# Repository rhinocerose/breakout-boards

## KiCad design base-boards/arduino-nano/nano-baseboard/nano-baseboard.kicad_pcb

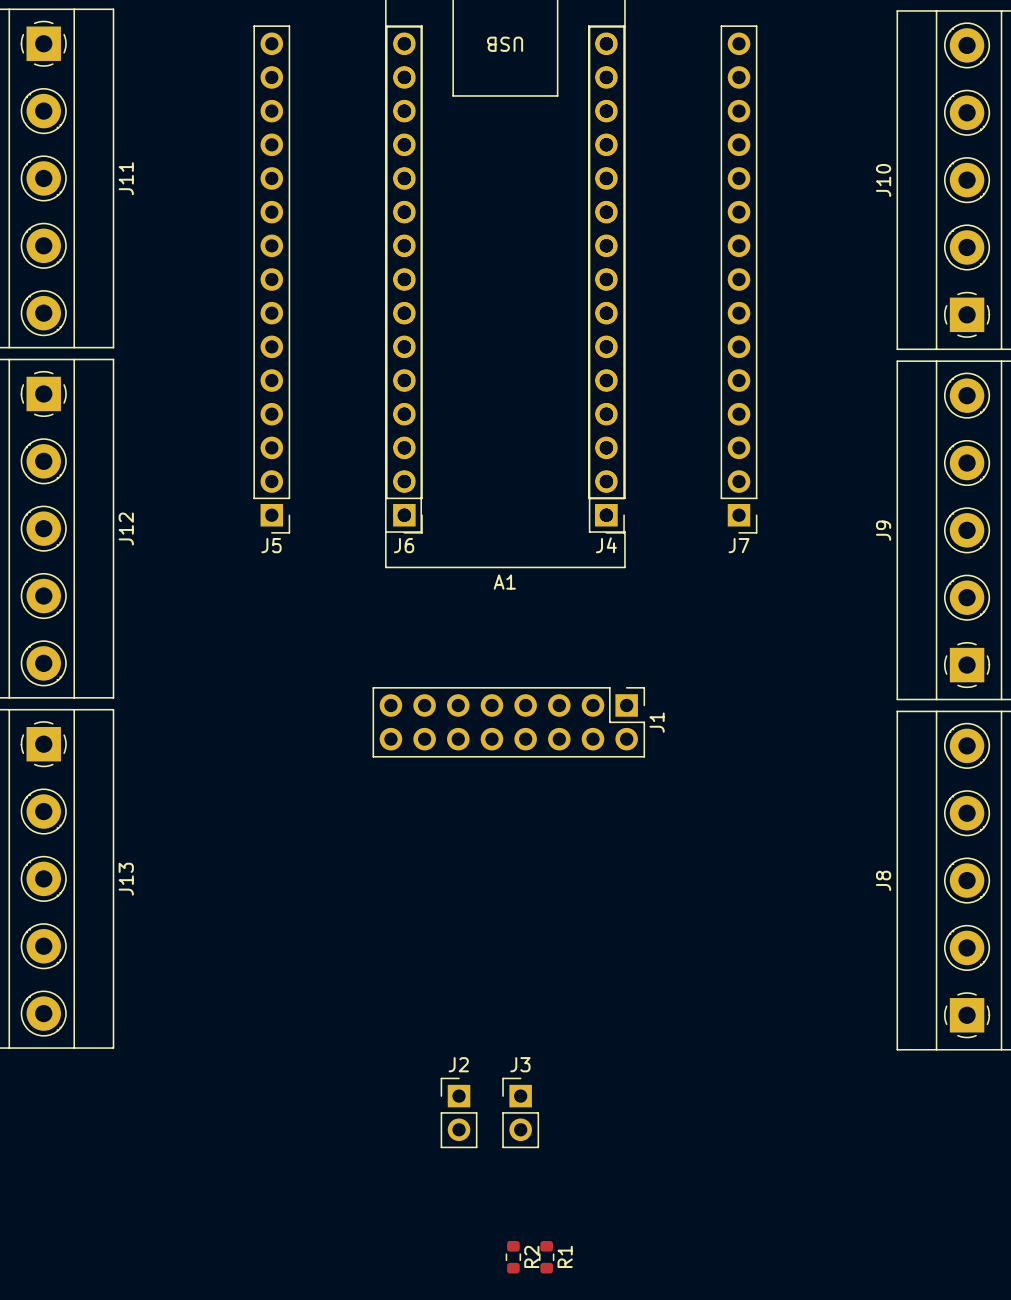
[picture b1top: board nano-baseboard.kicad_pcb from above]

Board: 2 copper layers, 16 parts (0 on the bottom side), 30 nets.

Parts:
A1: Arduino_Nano_v3.x; Arduino_Nano
J1: Conn_02x08_Odd_Even; PinHeader_2x08_P2.54mm_Vertical
J2, J3: Conn_01x02_Pin; PinHeader_1x02_P2.54mm_Vertical
J4, J5, J6, J7: Conn_01x15; PinHeader_1x15_P2.54mm_Vertical
J8, J9, J10, J11, J12, J13: Screw_Terminal_01x05; TerminalBlock_Phoenix_MKDS-1,5-5-5.08_1x05_P5.08mm_Horizont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
R1, R2: R_Small_US; R_0603_1608Metric

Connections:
3v3: A1.17 (3V3), J1.1, J1.2, J5.14, J6.14, J11.2
5v: A1.27 (+5V), J1.3, J1.4, J2.1, J3.1, J5.4, J6.4, J13.2
GND: A1.4 (GND), A1.29 (GND), J1.5, J1.6, J4.4, J5.2, J6.2, J7.4, J8.4, J13.4
I2C_SCL: A1.24 (A5), J1.8, J5.7, J6.7, J12.4, R2.2
I2C_SDA: A1.23 (A4), J1.7, J5.8, J6.8, J12.3, R1.2
unnamed: A1.19 (A0), J5.12, J6.12, J11.4
unnamed: A1.20 (A1), J5.11, J6.11, J11.5
unnamed: A1.21 (A2), J5.10, J6.10, J12.1
unnamed: A1.22 (A3), J5.9, J6.9, J12.2
unnamed: A1.25 (A6), J5.6, J6.6, J12.5
unnamed: A1.26 (A7), J5.5, J6.5, J13.1
unnamed: A1.18 (AREF), J5.13, J6.13, J11.3
unnamed: A1.2 (D0/RX), J4.2, J7.2, J8.2
unnamed: A1.1 (D1/TX), J4.1, J7.1, J8.1
unnamed: A1.5 (D2), J4.5, J7.5, J8.5
unnamed: A1.6 (D3), J4.6, J7.6, J9.1
unnamed: A1.7 (D4), J4.7, J7.7, J9.2
unnamed: A1.8 (D5), J4.8, J7.8, J9.3
unnamed: A1.9 (D6), J4.9, J7.9, J9.4
unnamed: A1.10 (D7), J4.10, J7.10, J9.5
unnamed: A1.11 (D8), J4.11, J7.11, J10.1
unnamed: A1.12 (D9), J4.12, J7.12, J10.2
unnamed: A1.13 (D10), J4.13, J7.13, J10.3
unnamed: J2.2, R1.1
unnamed: J3.2, R2.1
unnamed: J5.1, J6.1, J13.5
RST: A1.3 (~RESET), A1.28 (~RESET), J4.3, J5.3, J6.3, J7.3, J8.3, J13.3
SPI_MISO: A1.15 (D12), J1.10, J4.15, J7.15, J10.5
SPI_MOSI: A1.14 (D11), J1.9, J4.14, J7.14, J10.4
SPI_SCK: A1.16 (D13), J1.11, J5.15, J6.15, J11.1

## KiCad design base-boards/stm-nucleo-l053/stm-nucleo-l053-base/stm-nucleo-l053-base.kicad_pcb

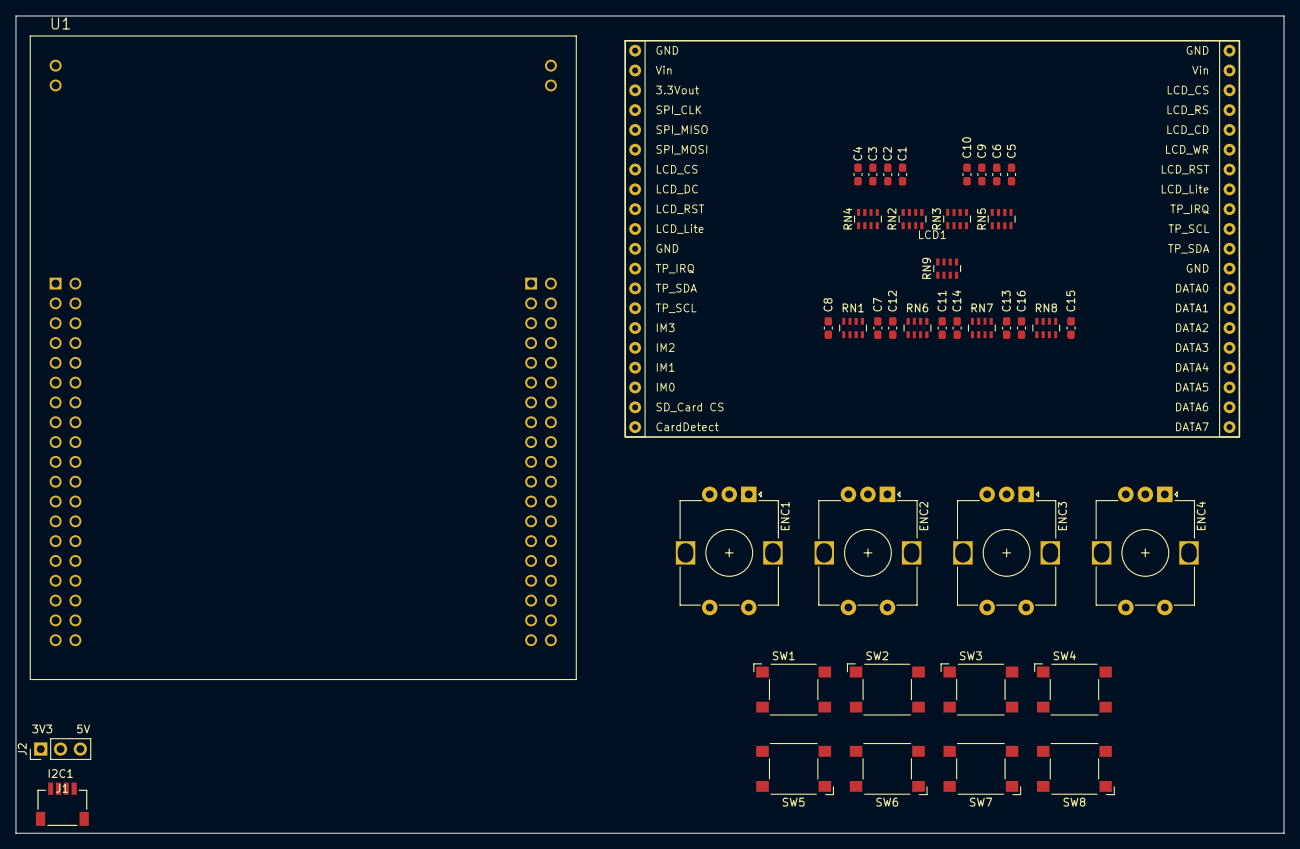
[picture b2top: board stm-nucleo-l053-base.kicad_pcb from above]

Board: 2 copper layers, 162.6 x 104.8 mm, 41 parts (0 on the bottom side), 50 nets, no tracks yet.

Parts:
C1, C2, C3, C4, C5, C6, C9, C10: 10uF; C_0603_1608Metric_Pad1.08x0.95mm_HandSolder
C7, C8, C11, C12, C13, C14, C15, C16: 10nF; C_0603_1608Metric_Pad1.08x0.95mm_HandSolder
ENC1, ENC2, ENC3, ENC4: RotaryEncoder_Switch; RotaryEncoder_Alps_EC12E-Switch_Vertical_H20mm
J1: Qwiic-SM04B-SRSS-TBLFSN; CONN_Qwiic_SM04B_JST
J2: Conn_01x03; PinHeader_1x03_P2.54mm_Vertical
LCD1: Adafruit_2090_Display
RN1, RN2, RN3, RN6, RN7, RN8: 10k_Parallel; R_Array_Concave_4x0603
RN4, RN5: 1k_Parallel; R_Array_Concave_4x0603
RN9: 4k7_Parallel; R_Array_Concave_4x0603
SW1, SW2, SW3, SW4, SW5, SW6, SW7, SW8: SW_SPST; SW_SPST_Omron_B3FS-101xP
U1: NUCLEO-L053R8; MODULE_NUCLEO-L053R8

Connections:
+3.3V: RN1.6 (R3.2), RN1.7 (R2.2), RN2.5 (R4.2), RN2.6 (R3.2), RN2.7 (R2.2), RN2.8 (R1.2), RN3.5 (R4.2), RN3.6 (R3.2), RN3.7 (R2.2), RN3.8 (R1.2), RN6.6 (R3.2), RN6.7 (R2.2), RN7.6 (R3.2), RN7.7 (R2.2), RN8.6 (R3.2), RN8.7 (R2.2), RN9.5 (R4.2), RN9.6 (R3.2), RN9.7 (R2.2), RN9.8 (R1.2)
+3V3: J2.1, U1.CN7_16 (+3V3)
+5V: J2.3, LCD1.2 (Vin), U1.CN7_18 (+5V)
BUTTON1: C1.2, RN4.1 (R1.1)
BUTTON2: C2.2, RN4.2 (R2.1)
BUTTON3: C3.2, RN4.3 (R3.1)
BUTTON4: C4.2, RN4.4 (R4.1)
BUTTON5: C5.2, RN5.1 (R1.1)
BUTTON6: C6.2, RN5.2 (R2.1)
BUTTON7: C9.2, RN5.3 (R3.1)
BUTTON8: C10.2, RN5.4 (R4.1)
ENC1_A: C7.1, RN1.5 (R4.2)
ENC1_B: C8.1, RN1.8 (R1.2)
ENC1_BUTTON: ENC1.S2, RN9.1 (R1.1)
ENC2_A: C11.1, RN6.5 (R4.2)
ENC2_B: C12.1, RN6.8 (R1.2)
ENC2_BUTTON: ENC2.S2, RN9.2 (R2.1)
ENC3_A: C13.1, RN7.5 (R4.2)
ENC3_B: C14.1, RN7.8 (R1.2)
ENC3_BUTTON: ENC3.S2, RN9.3 (R3.1)
ENC4_A: C15.1, RN8.5 (R4.2)
ENC4_B: C16.1, RN8.8 (R1.2)
ENC4_BUTTON: ENC4.S2, RN9.4 (R4.1)
GND: C1.1, C2.1, C3.1, C4.1, C5.1, C6.1, C7.2, C8.2, C9.1, C10.1, C11.2, C12.2, C13.2, C14.2, C15.2, C16.2, ENC1.C, ENC1.S1, ENC2.C, ENC2.S1, ENC3.C, ENC3.S1, ENC4.C, ENC4.S1, J1.1, LCD1.1 (GND), SW1.2 (B), SW2.2 (B), SW3.2 (B), SW4.2 (B), SW5.2 (B), SW6.2 (B), SW7.2 (B), SW8.2 (B), U1.CN7_8 (GND_8), U1.CN7_19 (GND_19), U1.CN7_20 (GND_20), U1.CN7_22 (GND_22), U1.CN10_9 (GND_9), U1.CN10_20 (GND_20), U1.CN11_1 (GND_CN11_1), U1.CN11_2 (GND_CN11_2), U1.CN12_1 (GND_CN12_1), U1.CN12_2 (GND_CN12_2)
I2C1_SCL: J1.4, LCD1.14 (TP_SCL), U1.CN10_3 (PB8)
I2C1_SDA: J1.3, LCD1.13 (TP_SDA), U1.CN10_5 (PB9)
LCD_CS: LCD1.7 (LCD_CS), U1.CN10_4 (PC6)
LCD_DC: LCD1.8 (LCD_DC), U1.CN10_6 (PC5)
LCD_LITE: LCD1.10 (LCD_Lite), U1.CN10_15 (PA7)
LCD_RST: LCD1.9 (LCD_RST), U1.CN10_13 (PA6)
unnamed: J1.2, J2.2
unnamed: ENC1.B, RN1.1 (R1.1), RN1.2 (R2.1)
unnamed: ENC1.A, RN1.3 (R3.1), RN1.4 (R4.1)
unnamed: RN2.1 (R1.1), RN4.8 (R1.2), SW1.1 (A)
unnamed: RN2.2 (R2.1), RN4.7 (R2.2), SW2.1 (A)
unnamed: RN2.3 (R3.1), RN4.6 (R3.2), SW3.1 (A)
unnamed: RN2.4 (R4.1), RN4.5 (R4.2), SW4.1 (A)
unnamed: RN3.1 (R1.1), RN5.8 (R1.2), SW5.1 (A)
unnamed: RN3.2 (R2.1), RN5.7 (R2.2), SW6.1 (A)
unnamed: RN3.3 (R3.1), RN5.6 (R3.2), SW7.1 (A)
unnamed: RN3.4 (R4.1), RN5.5 (R4.2), SW8.1 (A)
unnamed: ENC2.B, RN6.1 (R1.1), RN6.2 (R2.1)
unnamed: ENC2.A, RN6.3 (R3.1), RN6.4 (R4.1)
unnamed: ENC3.B, RN7.1 (R1.1), RN7.2 (R2.1)
unnamed: ENC3.A, RN7.3 (R3.1), RN7.4 (R4.1)
unnamed: ENC4.B, RN8.1 (R1.1), RN8.2 (R2.1)
unnamed: ENC4.A, RN8.3 (R3.1), RN8.4 (R4.1)
SPI1_MISO: LCD1.5 (SPI_MISO), U1.CN10_27 (PB4)
SPI1_MOSI: LCD1.6 (SPI_MOSI), U1.CN10_29 (PB5)
SPI1_SCK: LCD1.4 (SPI_CLK), U1.CN10_31 (PB3)

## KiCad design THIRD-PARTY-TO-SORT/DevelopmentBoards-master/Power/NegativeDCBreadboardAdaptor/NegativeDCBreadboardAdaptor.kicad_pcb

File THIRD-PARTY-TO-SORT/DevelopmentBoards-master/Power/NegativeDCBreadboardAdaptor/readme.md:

<h2> Low current TC7660S-based Bipolar Regulator </h2>

Designed to sit over central divide on a breadboard. For development purpose only.
<br><br>
Uses charge pump DC-DC converter ([TC7660S](http://ww1.microchip.com/downloads/en/DeviceDoc/20001467C.pdf)) to create negative voltage. 
<br><br>Maximum current draw of 50mA is recommended - although the datasheet is vague in explicitly stating absolute maximum limits. 
<br><br>
Switching frequency raised to 45 kHz to prevent audible noise. 

<h3>Schematic</h3>

<h3>3D Renders</h3>

<h3> Board Layout</h3>

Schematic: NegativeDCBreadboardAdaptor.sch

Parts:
C_BP1: 2.2uF; CP_Elec_4x5.3
C_BP2: 100nF; CP_Elec_4x5.3
C_NEG1, C_NEG2: 10uF; CP_Elec_4x5.3
J_IN1: Conn_01x05; Pin_Header_Straight_1x05_Pitch2.54mm
J_OUT1: Conn_01x05; Pin_Header_Straight_1x05_Pitch2.54mm
U_NEGDC1: _TC7662B; SOIC-8-N

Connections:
/GND: C_BP1.2, C_BP2.2, C_NEG2.1, J_IN1.5, J_OUT1.5, U_NEGDC1.3, U_NEGDC1.6
unnamed: C_BP1.1, C_BP2.1, J_IN1.1, J_OUT1.1, U_NEGDC1.1, U_NEGDC1.8
unnamed: C_NEG1.1, U_NEGDC1.2
unnamed: C_NEG1.2, U_NEGDC1.4
unnamed: C_NEG2.2, J_OUT1.3, U_NEGDC1.5

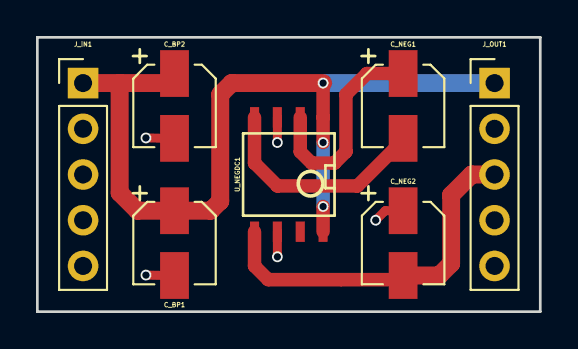
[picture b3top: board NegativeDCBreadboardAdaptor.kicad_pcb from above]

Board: 2 copper layers, 27.9 x 15.2 mm, 7 parts (0 on the bottom side), 5 nets.

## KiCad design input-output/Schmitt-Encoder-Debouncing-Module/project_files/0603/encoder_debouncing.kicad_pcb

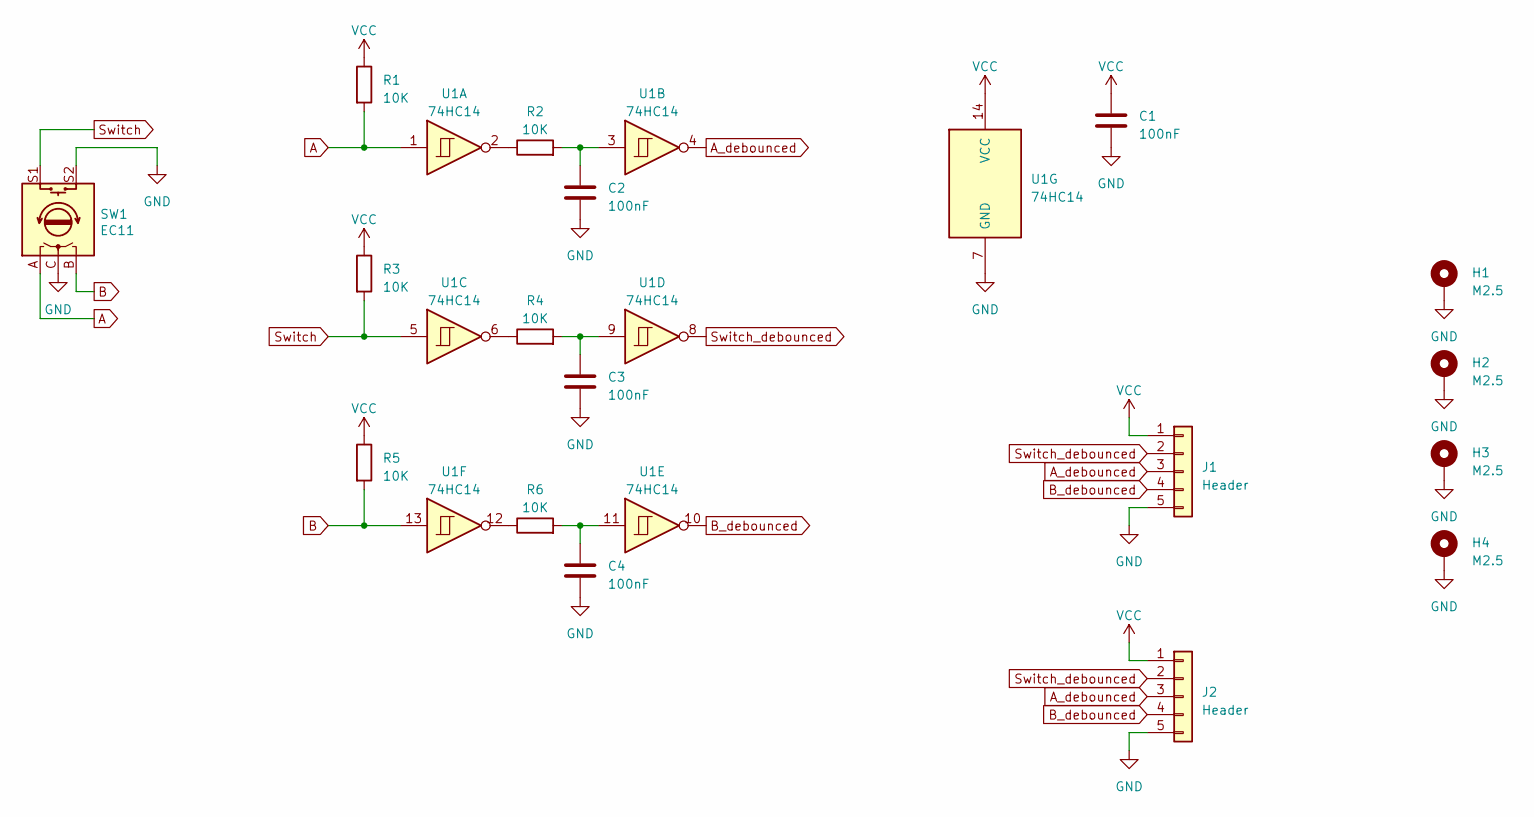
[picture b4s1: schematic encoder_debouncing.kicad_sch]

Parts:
C1, C2, C3, C4: 100nF; C_0603_1608Metric_Pad1.08x0.95mm_HandSolder
H1, H2, H3, H4: M2.5; MountingHole_2.7mm_M2.5_ISO7380_Pad_TopBottom
J1, J2: Header; PinHeader_1x05_P2.54mm_Vertical
R1, R2, R3, R4, R5, R6: 10K; R_0603_1608Metric_Pad0.98x0.95mm_HandSolder
SW1: EC11; RotaryEncoder_Alps_EC11E-Switch_Vertical_H20mm
U1: 74HC14; SOIC-14_3.9x8.7mm_P1.27mm

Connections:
A: R1.2, SW1.A, U1.1
A_debounced: J1.3, J2.3, U1.4
B: R5.2, SW1.B, U1.13
B_debounced: J1.4, J2.4, U1.10
GND: C1.2, C2.2, C3.2, C4.2, H1.1, H2.1, H3.1, H4.1, J1.5, J2.5, SW1.C, SW1.S2, U1.7 (GND)
unnamed: C2.1, R2.2, U1.3
unnamed: C3.1, R4.2, U1.9
unnamed: C4.1, R6.2, U1.11
unnamed: R2.1, U1.2
unnamed: R4.1, U1.6
unnamed: R6.1, U1.12
Switch: R3.2, SW1.S1, U1.5
Switch_debounced: J1.2, J2.2, U1.8
VCC: C1.1, J1.1, J2.1, R1.1, R3.1, R5.1, U1.14 (VCC)

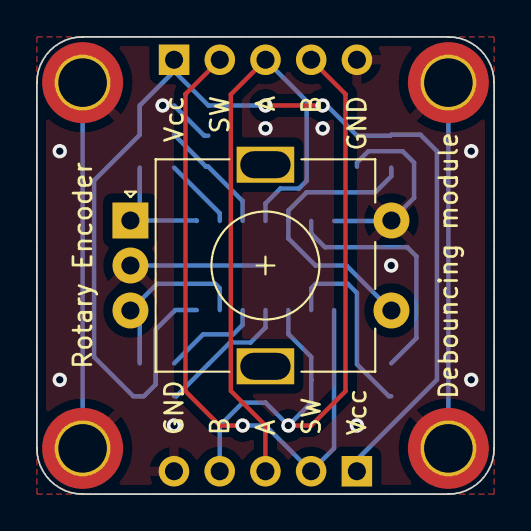
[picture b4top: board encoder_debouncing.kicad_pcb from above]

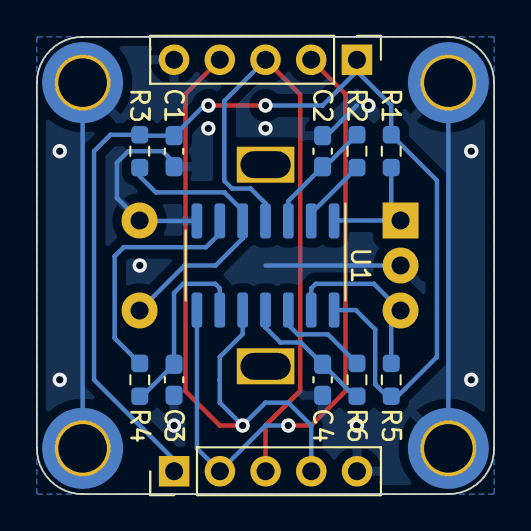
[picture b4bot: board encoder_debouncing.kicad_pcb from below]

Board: 2 copper layers, 25.4 x 25.4 mm, 18 parts (13 on the bottom side), 14 nets.

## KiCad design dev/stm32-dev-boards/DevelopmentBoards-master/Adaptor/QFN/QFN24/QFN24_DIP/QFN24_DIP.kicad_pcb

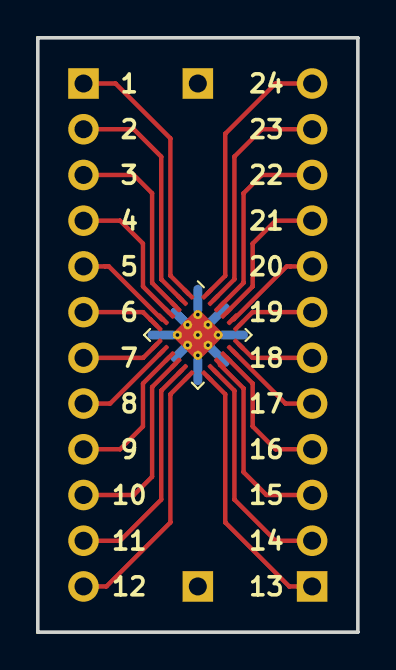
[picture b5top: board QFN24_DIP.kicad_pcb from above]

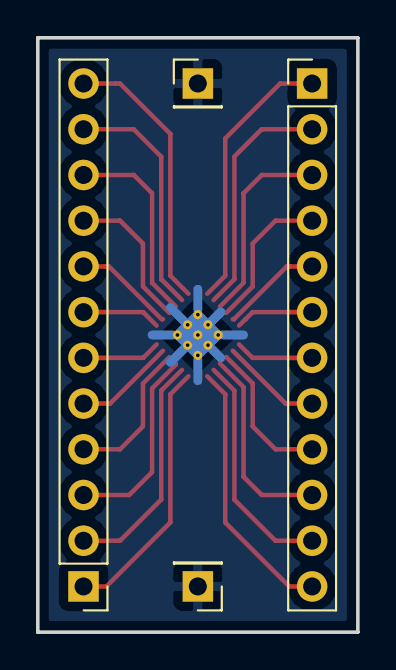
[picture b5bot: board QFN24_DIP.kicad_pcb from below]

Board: 2 copper layers, 17.8 x 33.0 mm, 5 parts (4 on the bottom side), 25 nets.

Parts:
J1, J2: Conn_01x12; PinHeader_1x12_P2.54mm_Vertical
J3, J4: Conn_01x01; PinHeader_1x01_P2.54mm_Vertical
U1: DummyQFN24; Texas_S-PVQFN-N24_EP2.1x2.1mm_ThermalVias

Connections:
/1: J1.1, U1.1
/2: J1.2, U1.2
/3: J1.3, U1.3
/4: J1.4, U1.4
/5: J1.5, U1.5
/6: J1.6, U1.6
/7: J1.7, U1.7
/8: J1.8, U1.8
/9: J1.9, U1.9
/10: J1.10, U1.10
/11: J1.11, U1.11
/12: J1.12, U1.12
/13: J2.1, U1.13
/14: J2.2, U1.14
/15: J2.3, U1.15
/16: J2.4, U1.16
/17: J2.5, U1.17
/18: J2.6, U1.18
/19: J2.7, U1.19
/20: J2.8, U1.20
/21: J2.9, U1.21
/22: J2.10, U1.22
/23: J2.11, U1.23
/24: J2.12, U1.24
/THERMALPAD: J3.1, J4.1, U1.25

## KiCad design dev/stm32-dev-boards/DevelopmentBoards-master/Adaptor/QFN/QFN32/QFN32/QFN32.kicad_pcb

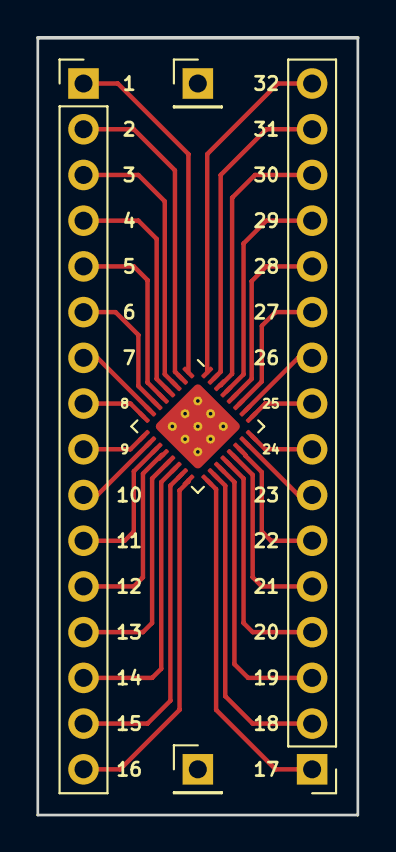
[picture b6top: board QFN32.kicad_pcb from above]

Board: 2 copper layers, 17.8 x 43.2 mm, 5 parts (0 on the bottom side), 33 nets.

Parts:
J1, J2: Conn_01x01; PinHeader_1x01_P2.54mm_Vertical
J3, J4: Conn_01x16; PinHeader_1x16_P2.54mm_Vertical
U1: DummyQFN32; Texas_S-PVQFN-N32_EP3.45x3.45mm_ThermalVias

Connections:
/1: J3.1, U1.1
/2: J3.2, U1.2
/3: J3.3, U1.3
/4: J3.4, U1.4
/5: J3.5, U1.5
/6: J3.6, U1.6
/7: J3.7, U1.7
/8: J3.8, U1.8
/9: J3.9, U1.9
/10: J3.10, U1.10
/11: J3.11, U1.11
/12: J3.12, U1.12
/13: J3.13, U1.13
/14: J3.14, U1.14
/15: J3.15, U1.15
/16: J3.16, U1.16
/17: J4.1, U1.17
/18: J4.2, U1.18
/19: J4.3, U1.19
/20: J4.4, U1.20
/21: J4.5, U1.21
/22: J4.6, U1.22
/23: J4.7, U1.23
/24: J4.8, U1.24
/25: J4.9, U1.25
/26: J4.10, U1.26
/27: J4.11, U1.27
/28: J4.12, U1.28
/29: J4.13, U1.29
/30: J4.14, U1.30
/31: J4.15, U1.31
/32: J4.16, U1.32
/THERMAL_PAD: J1.1, J2.1, U1.33

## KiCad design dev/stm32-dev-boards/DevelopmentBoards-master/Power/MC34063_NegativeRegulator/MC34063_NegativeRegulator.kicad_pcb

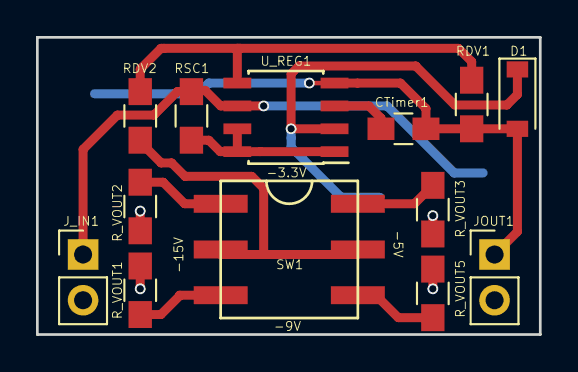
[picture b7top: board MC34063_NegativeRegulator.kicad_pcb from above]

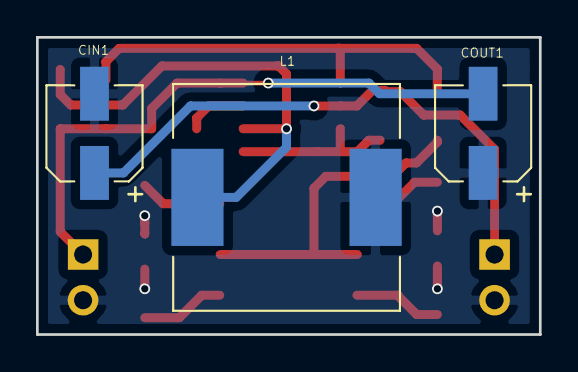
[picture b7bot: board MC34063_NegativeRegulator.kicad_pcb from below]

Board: 2 copper layers, 27.9 x 16.5 mm, 16 parts (3 on the bottom side), 12 nets.

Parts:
CIN1: 100uF; CP_Elec_5x5.8
COUT1: 100uF; CP_Elec_5x5.8
CTimer1: 220pF; C_0805_HandSoldering
D1: 1N5819; D_SOD-123
JOUT1: Conn_01x02; Pin_Header_Straight_1x02_Pitch2.54mm
J_IN1: Conn_01x02; Pin_Header_Straight_1x02_Pitch2.54mm
L1: 100uH; L_12x12mm_h8mm
RDV1: 10K; R_0805_HandSoldering
RDV2: 1K; R_0805_HandSoldering
RSC1: 0.5R; R_0805_HandSoldering
R_VOUT1: 16K; R_0805_HandSoldering
R_VOUT2: 30K; R_0805_HandSoldering
R_VOUT3: 60K; R_0805_HandSoldering
R_VOUT5: 112K; R_0805_HandSoldering
SW1: SW_Rotary4; RotarySW_CTS_SERIES_220AD_04_SMT_4Position
U_REG1: MC34063; SOIC-8_3.9x4.9mm_Pitch1.27mm

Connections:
/GND: CIN1.2, COUT1.1, JOUT1.2, J_IN1.2, L1.1, R_VOUT1.2, R_VOUT2.2, R_VOUT3.2, R_VOUT5.2
/VNEG: COUT1.2, CTimer1.1, D1.2, JOUT1.1, RDV1.2, U_REG1.4
unnamed: CIN1.1, J_IN1.1, RSC1.2, U_REG1.6
unnamed: CTimer1.2, U_REG1.3
unnamed: D1.1, L1.2, U_REG1.2
unnamed: RDV1.1, RDV2.1, U_REG1.5
unnamed: RDV2.2, SW1.4
unnamed: RSC1.1, U_REG1.1, U_REG1.7, U_REG1.8
unnamed: R_VOUT1.1, SW1.0
unnamed: R_VOUT2.1, SW1.1
unnamed: R_VOUT3.1, SW1.2
unnamed: R_VOUT5.1, SW1.3

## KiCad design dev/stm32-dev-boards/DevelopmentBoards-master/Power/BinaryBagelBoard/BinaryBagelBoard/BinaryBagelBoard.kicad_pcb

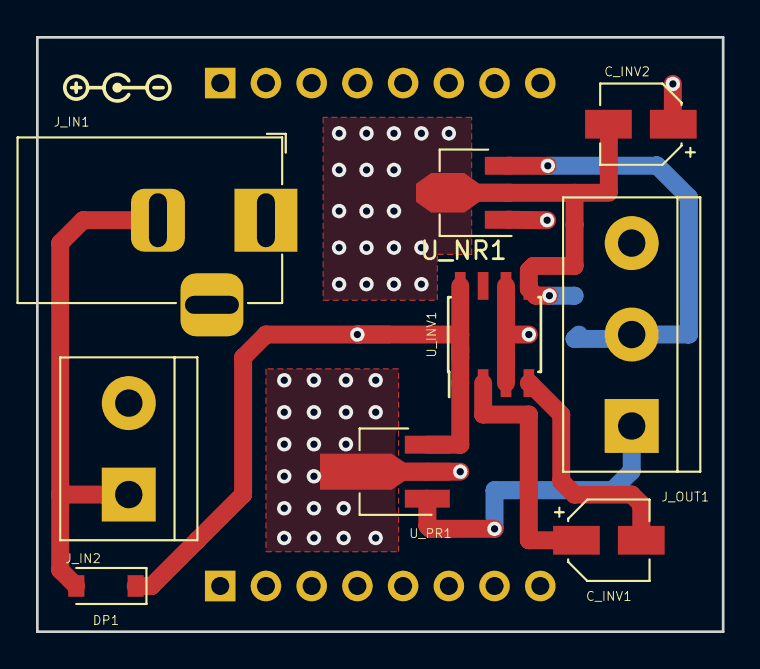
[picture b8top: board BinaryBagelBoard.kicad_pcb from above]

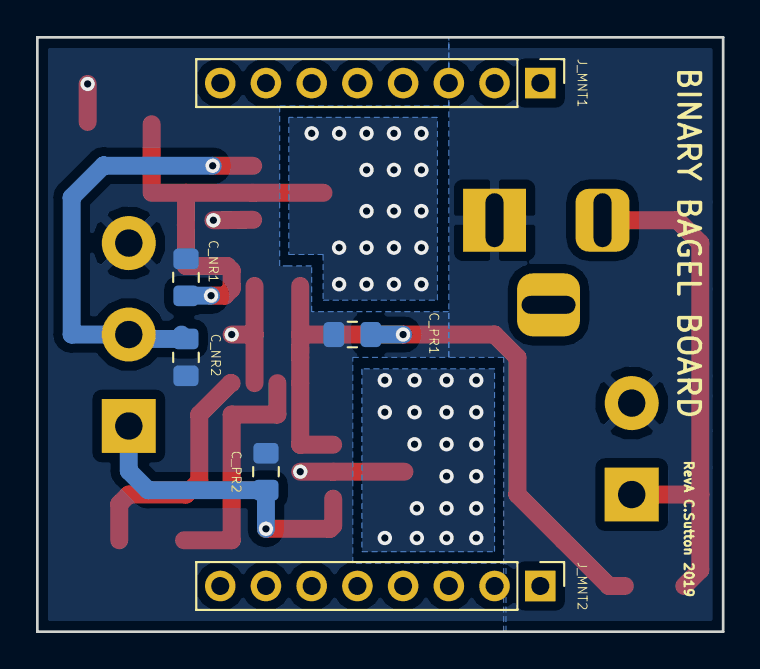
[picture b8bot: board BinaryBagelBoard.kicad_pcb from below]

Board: 2 copper layers, 38.1 x 33.0 mm, 15 parts (6 on the bottom side), 8 nets.

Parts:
C_INV1, C_INV2: 10uF; CP_Elec_4x5.7
C_NR1: 330nF; C_0805_2012Metric_Pad1.15x1.40mm_HandSolder
C_NR2: 100nF; C_0805_2012Metric_Pad1.15x1.40mm_HandSolder
C_PR1: 330nF; C_0805_2012Metric_Pad1.15x1.40mm_HandSolder
C_PR2: 100nF; C_0805_2012Metric_Pad1.15x1.40mm_HandSolder
DP1: D_Schottky; D_SOD-123
J_IN1: Barrel_Jack; BarrelJack_Horizontal
J_IN2: Conn_01x02; TerminalBlock_bornier-2_P5.08mm
J_MNT1, J_MNT2: Conn_01x08; PinHeader_1x08_P2.54mm_Vertical
J_OUT1: Conn_01x03; TerminalBlock_bornier-3_P5.08mm
U_INV1: TC7662BxPA; SOIC-8_3.9x4.9mm_P1.27mm
U_NR1: L79L05_SOT89; SOT-89-3
U_PR1: MC78L05_SOT89; SOT-89-3_Handsoldering

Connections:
/+5V: C_PR2.1, J_OUT1.1, U_PR1.1
/-5V: C_NR2.2, J_OUT1.2, U_NR1.3
/GND: C_INV2.1, C_NR1.1, C_NR2.1, C_PR1.2, C_PR2.2, J_IN1.1, J_IN2.2, J_OUT1.3, U_INV1.3, U_INV1.6, U_NR1.1, U_PR1.2
unnamed: C_INV1.1, U_INV1.2
unnamed: C_INV1.2, U_INV1.4
unnamed: C_INV2.2, C_NR1.2, U_INV1.5, U_NR1.2
unnamed: C_PR1.1, DP1.1, U_INV1.1, U_INV1.8, U_PR1.3
unnamed: DP1.2, J_IN1.2, J_IN2.1

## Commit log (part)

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2022-04-17 Only reset left to sort out
2022-04-17 Encoders added
2022-04-17 Added SD breakout
2022-04-17 Added pdf and images
2022-04-17 Added images
2022-04-18 Added accelerometer
2022-04-18 Added codecs
2022-04-19 Added dual encoder module
2022-04-19 Added datasheets and firmware
2022-04-19 Added DAC buffers to AD1938
2022-11-23 Dev folder added
2022-12-05 Renamed folders to not be hidden
2023-01-02 Added encoder
2023-01-02 Added I2C encoder
2023-02-06 Rearranged
2024-02-08 Added Nucleo base board
2024-11-15 Added Arduino Nano breakout
2025-08-12 Update submodules to track main branch
2025-08-12 Update submodules: set branch=main and fix URLs
2025-08-12 Update submodules: add branch=main and fix URLs
2025-08-13 Remove .gitmodules (no submodules exist)
